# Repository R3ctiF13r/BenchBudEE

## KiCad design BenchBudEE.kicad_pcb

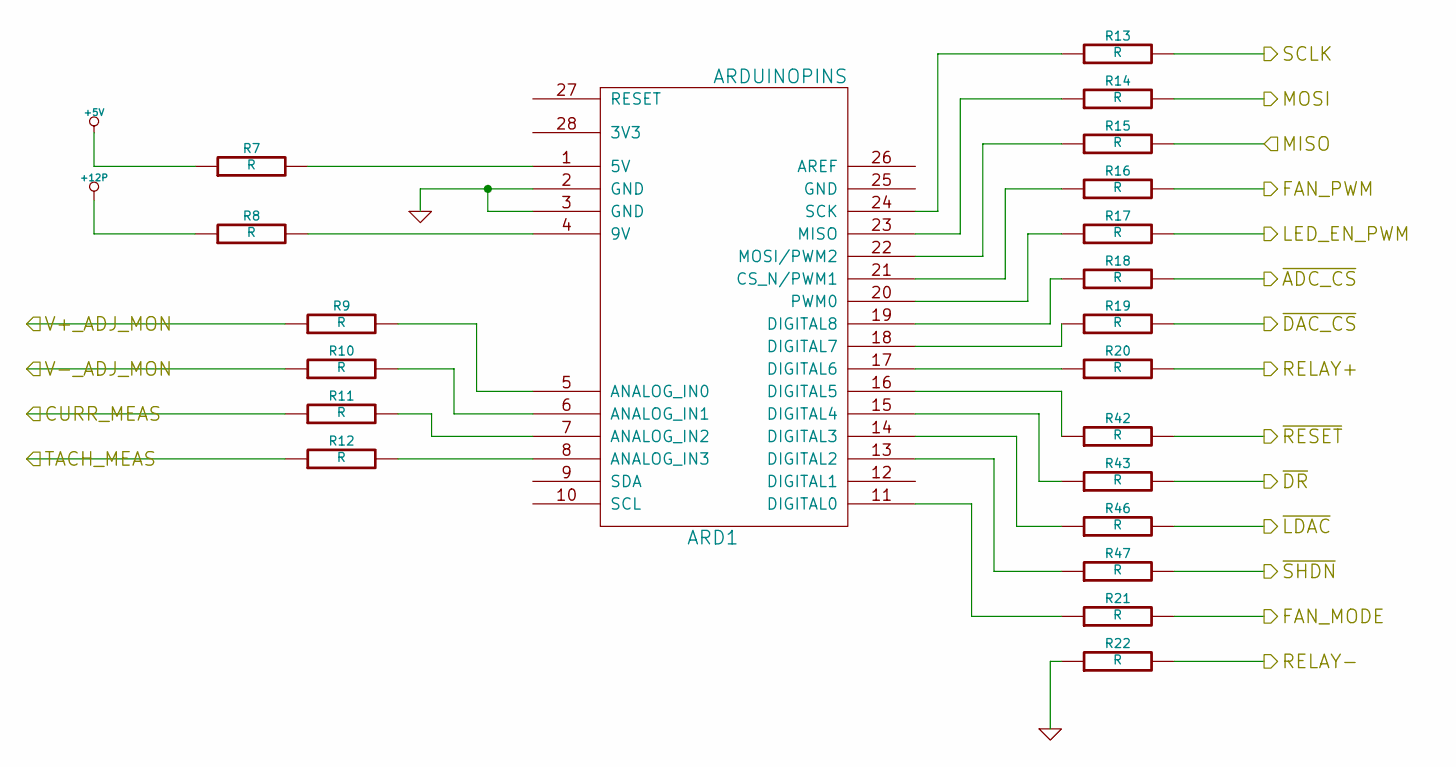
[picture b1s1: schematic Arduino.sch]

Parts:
ARD1: ARDUINOPINS
R7, R8, R9, R10, R11, R12, R13, R14, R15, R16, R17, R18, R19, R20, R21, R22, R42, R43, R46, R47: R

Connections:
+5V: R7.1; also elsewhere on the board
+12P: R8.1; also elsewhere on the board
/Arduino/CURR_MEAS: R11.1; also elsewhere on the board
/Arduino/FAN_MODE: R21.2; also elsewhere on the board
/Arduino/FAN_PWM: R16.2; also elsewhere on the board
/Arduino/LED_EN_PWM: R17.2; also elsewhere on the board
/Arduino/MISO: R15.2; also elsewhere on the board
/Arduino/MOSI: R14.2; also elsewhere on the board
/Arduino/RELAY+: R20.2; also elsewhere on the board
/Arduino/RELAY-: R22.2; also elsewhere on the board
/Arduino/SCLK: R13.2; also elsewhere on the board
/Arduino/V+_ADJ_MON: R9.1; also elsewhere on the board
/Arduino/V-_ADJ_MON: R10.1; also elsewhere on the board
/Arduino/~ADC_CS: R18.2; also elsewhere on the board
/Arduino/~DR: R43.2; also elsewhere on the board
/Arduino/~LDAC: R46.2; also elsewhere on the board
/Arduino/~RESET: R42.2; also elsewhere on the board
/Arduino/~SHDN: R47.2; also elsewhere on the board
/Fan/TACH: R12.1; also elsewhere on the board
/Fan/~CS: R19.2; also elsewhere on the board
GND: ARD1.2 (GND), ARD1.3 (GND), R22.1; also elsewhere on the board
unnamed: ARD1.6 (ANALOG_IN1), R10.2
unnamed: ARD1.5 (ANALOG_IN0), R9.2
unnamed: ARD1.22 (MOSI/PWM2), R15.1
unnamed: ARD1.23 (MISO), R14.1
unnamed: ARD1.24 (SCK), R13.1
unnamed: ARD1.8 (ANALOG_IN3), R12.2
unnamed: ARD1.7 (ANALOG_IN2), R11.2
unnamed: ARD1.14 (DIGITAL3), R46.1
unnamed: ARD1.20 (PWM0), R17.1
unnamed: ARD1.19 (DIGITAL8), R18.1
unnamed: ARD1.16 (DIGITAL5), R42.1
unnamed: ARD1.13 (DIGITAL2), R47.1
unnamed: ARD1.18 (DIGITAL7), R19.1
unnamed: ARD1.17 (DIGITAL6), R20.1
unnamed: ARD1.15 (DIGITAL4), R43.1
unnamed: ARD1.1 (5V), R7.2
unnamed: ARD1.21 (CS_N/PWM1), R16.1
unnamed: ARD1.11 (DIGITAL0), R21.1
unnamed: ARD1.4 (9V), R8.2

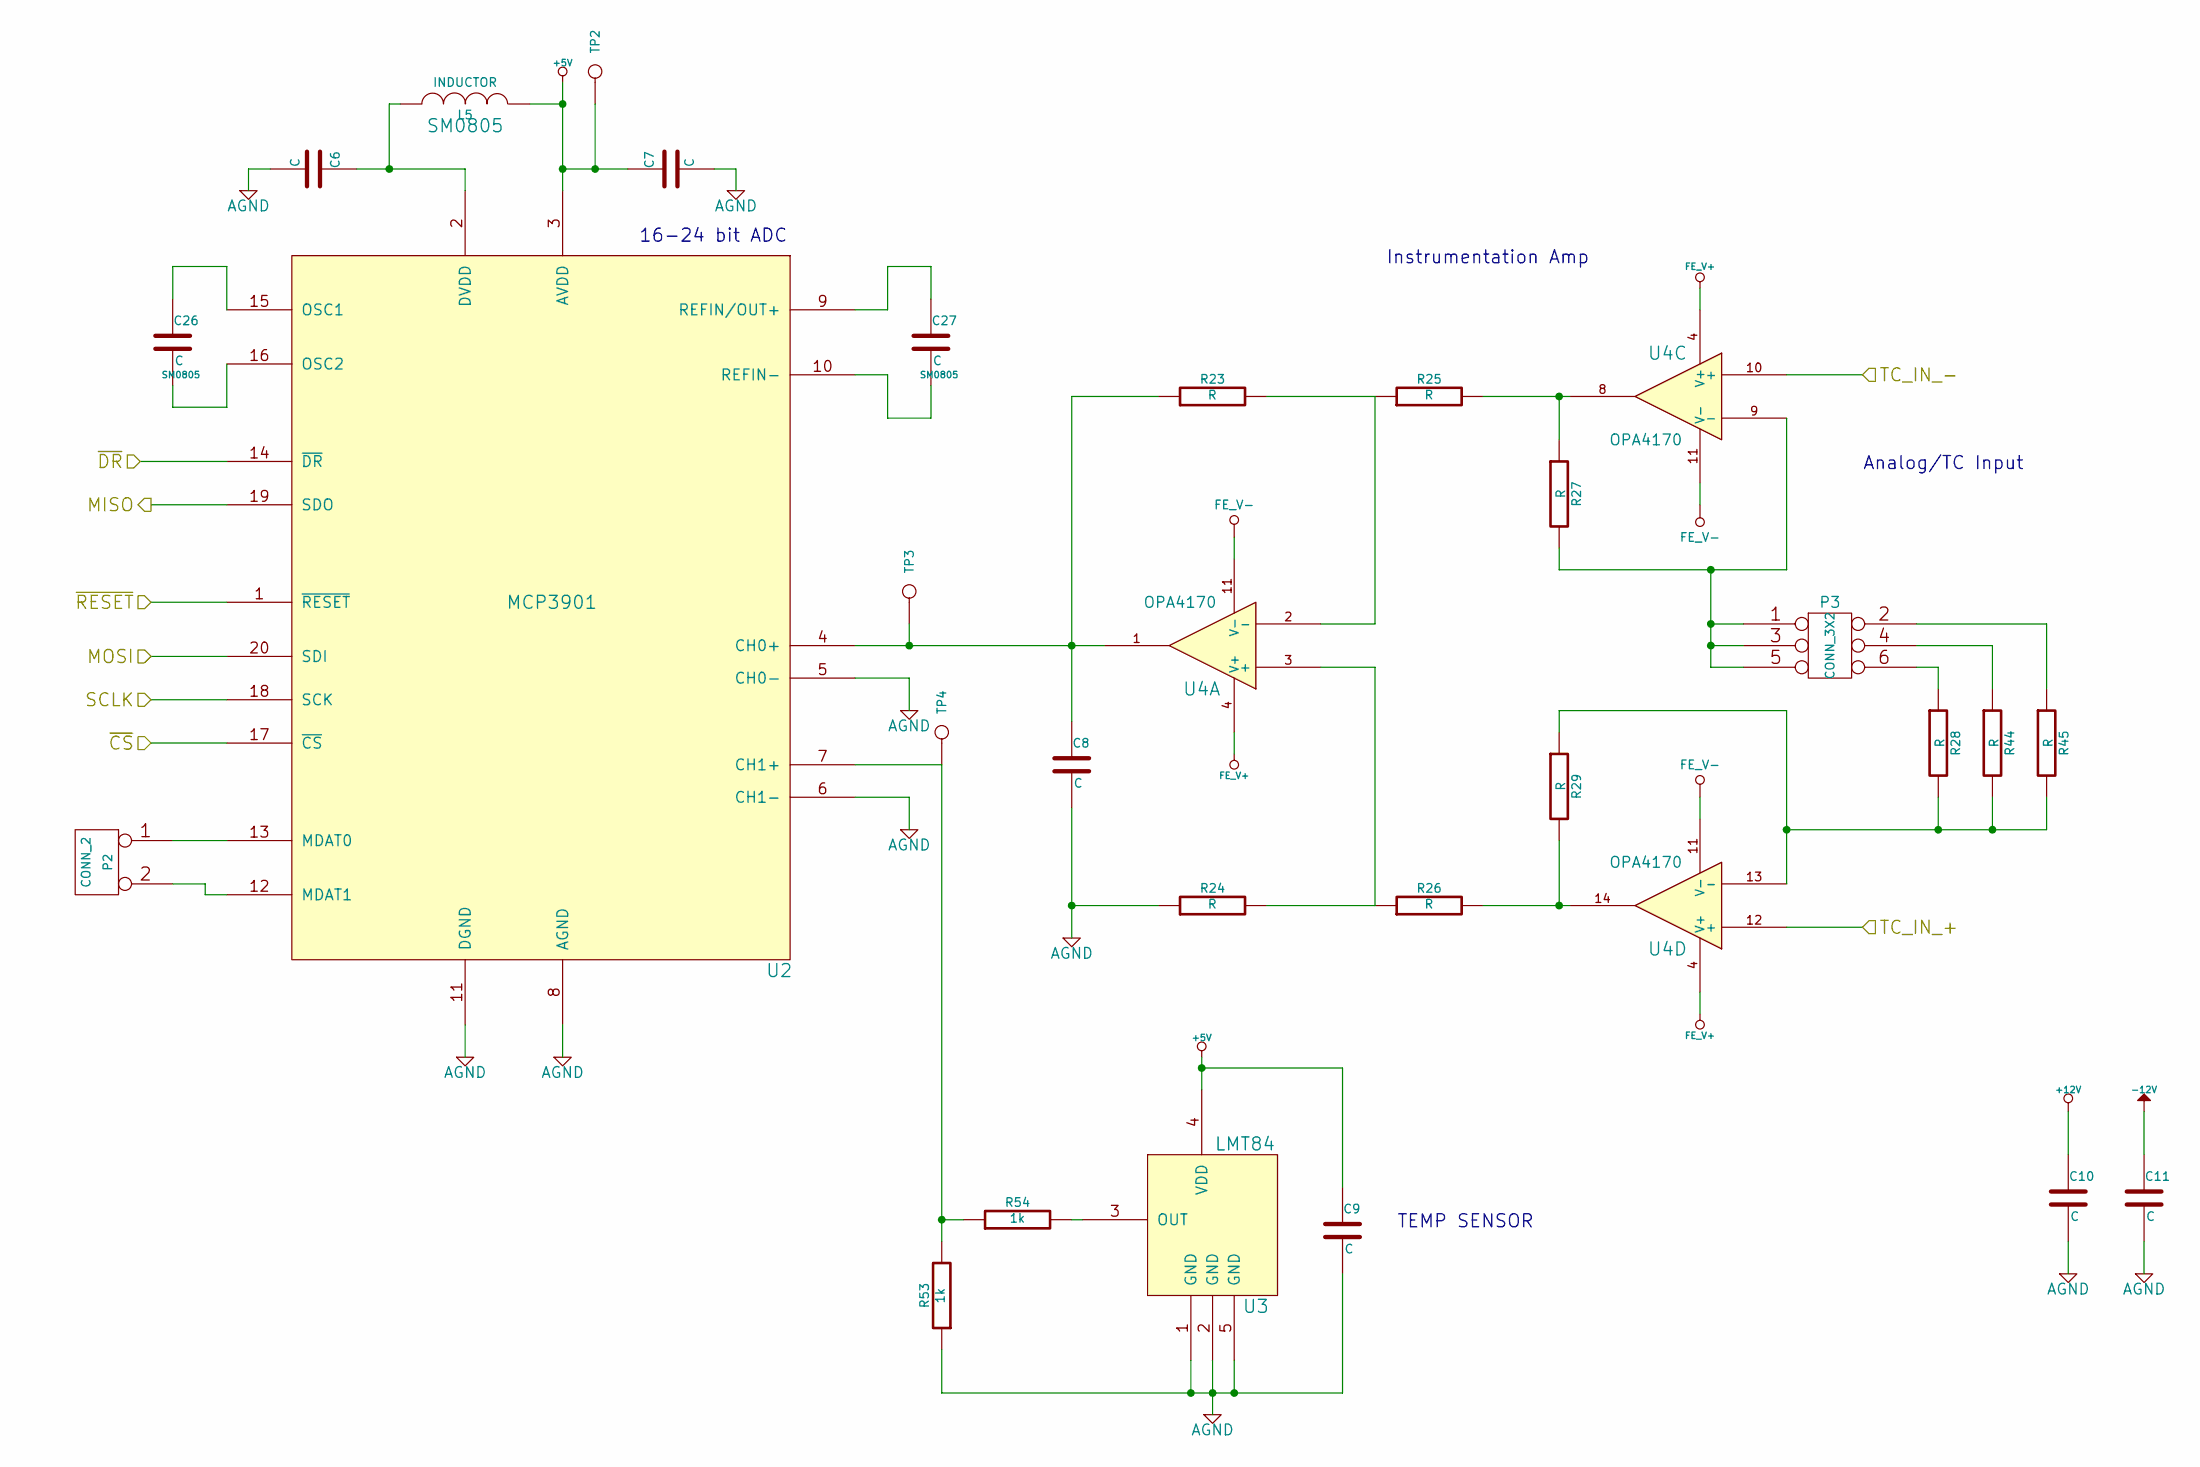
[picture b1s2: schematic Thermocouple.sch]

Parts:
C6, C7, C8, C9, C10, C11: C
C26, C27: C; SM0805
L5: INDUCTOR; SM0805
P2: CONN_2
P3: CONN_3X2
R23, R24, R25, R26, R27, R28, R29, R44, R45: R
R53, R54: 1k
TP2: +5V
TP3: CH0+
TP4: CH1+
U2: MCP3901
U3: LMT84
U4: OPA4170

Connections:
+5V: C7.1, C9.1, L5.1, TP2.1, U2.3 (AVDD), U3.4 (VDD); also elsewhere on the board
+12V: C10.1; also elsewhere on the board
-12V: C11.1; also elsewhere on the board
/Arduino/MISO: U2.19 (SDO); also elsewhere on the board
/Arduino/MOSI: U2.20 (SDI); also elsewhere on the board
/Arduino/SCLK: U2.18 (SCK); also elsewhere on the board
/Arduino/~ADC_CS: U2.17 (~CS); also elsewhere on the board
/Arduino/~DR: U2.14 (~DR); also elsewhere on the board
/Arduino/~RESET: U2.1 (~RESET); also elsewhere on the board
/Terminal_Block/TC_IN_+: U4.12 (+); also elsewhere on the board
/Terminal_Block/TC_IN_-: U4.10 (+); also elsewhere on the board
AGND: C6.2, C7.2, C8.2, C9.2, C10.2, C11.2, R24.1, R53.1, U2.5 (CH0-), U2.6 (CH1-), U2.8 (AGND), U2.11 (DGND), U3.1 (GND), U3.2 (GND), U3.5 (GND); also elsewhere on the board
FE_V+: U4.4 (V+); also elsewhere on the board
FE_V-: U4.11 (V-); also elsewhere on the board
unnamed: C27.1, U2.9 (REFIN/OUT+)
unnamed: C26.1, U2.15 (OSC1)
unnamed: C26.2, U2.16 (OSC2)
unnamed: P2.1, U2.13 (MDAT0)
unnamed: P2.2 (PM), U2.12 (MDAT1)
unnamed: C27.2, U2.10 (REFIN-)
unnamed: R53.2, R54.1, TP4.1, U2.7 (CH1+)
unnamed: R54.2, U3.3 (OUT)
unnamed: C6.1, L5.2, U2.2 (DVDD)
unnamed: C8.1, R23.1, TP3.1, U2.4 (CH0+), U4.1
unnamed: R24.2, R26.1, U4.3 (+)
unnamed: R23.2, R25.1, U4.2 (-)
unnamed: R25.2, R27.1, U4.8
unnamed: R26.2, R29.2, U4.14
unnamed: P3.6, R28.1
unnamed: P3.4, R44.1
unnamed: P3.1, P3.3, P3.5, R27.2, U4.9 (-)
unnamed: P3.2, R45.1
unnamed: R28.2, R29.1, R44.2, R45.2, U4.13 (-)

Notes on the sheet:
Analog/TC Input
Instrumentation Amp
16-24 bit ADC
TEMP SENSOR

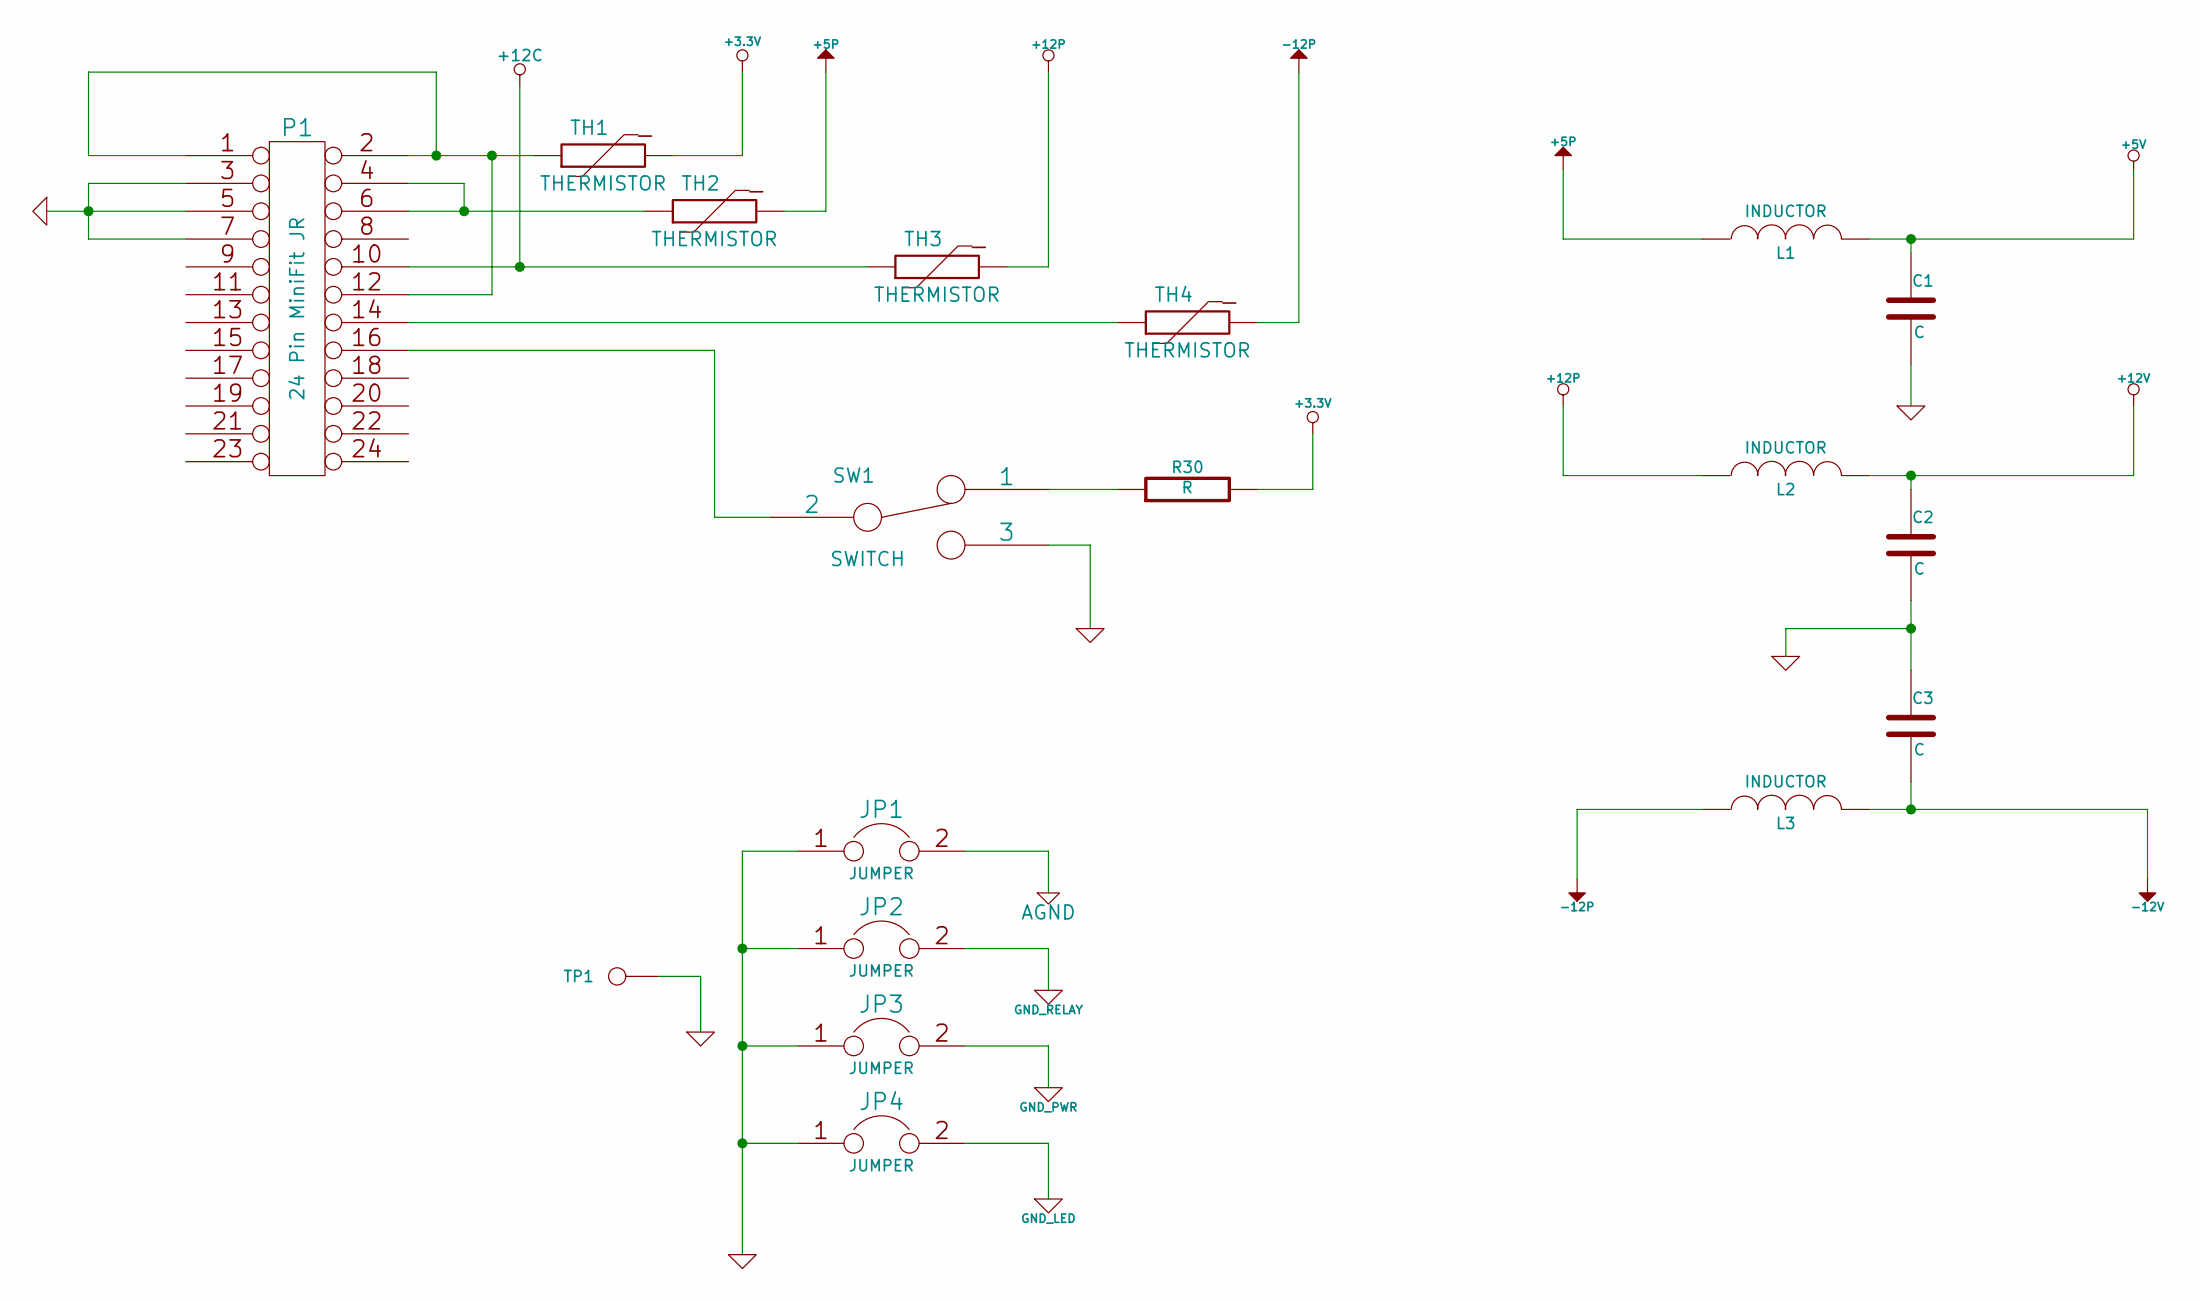
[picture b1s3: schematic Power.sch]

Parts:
C1, C2, C3: C
JP1, JP2, JP3, JP4: JUMPER
L1, L2, L3: INDUCTOR; MFG PART NUM CM322522-220KL
P1: 24 Pin MiniFit JR; MFG PART NUM 39-30-1240
R30: R
SW1: SWITCH; MFG PART NUM OS102011MA1QN1
TH1, TH2, TH3, TH4: THERMISTOR; MFG PART NUM MINISMDC050F-2
TP1: CONN_1

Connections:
+3.3V: R30.2, TH1.2; also elsewhere on the board
+5P: L1.1, TH2.2; also elsewhere on the board
+5V: C1.1, L1.2; also elsewhere on the board
+12C: P1.10, TH3.1; also elsewhere on the board
+12P: L2.1, TH3.2; also elsewhere on the board
+12V: C2.1, L2.2; also elsewhere on the board
-12P: L3.1, TH4.2
-12V: C3.2, L3.2; also elsewhere on the board
AGND: JP1.2; also elsewhere on the board
GND: C1.2, C2.2, C3.1, JP1.1, JP2.1, JP3.1, JP4.1, P1.3, P1.5, P1.7, SW1.3, TP1.1; also elsewhere on the board
GND_LED: JP4.2; also elsewhere on the board
GND_PWR: JP3.2; also elsewhere on the board
GND_RELAY: JP2.2; also elsewhere on the board
unnamed: P1.14, TH4.1
unnamed: P1.4, P1.6, TH2.1
unnamed: R30.1, SW1.1
unnamed: P1.16, SW1.2
unnamed: P1.1, P1.2, P1.12, TH1.1

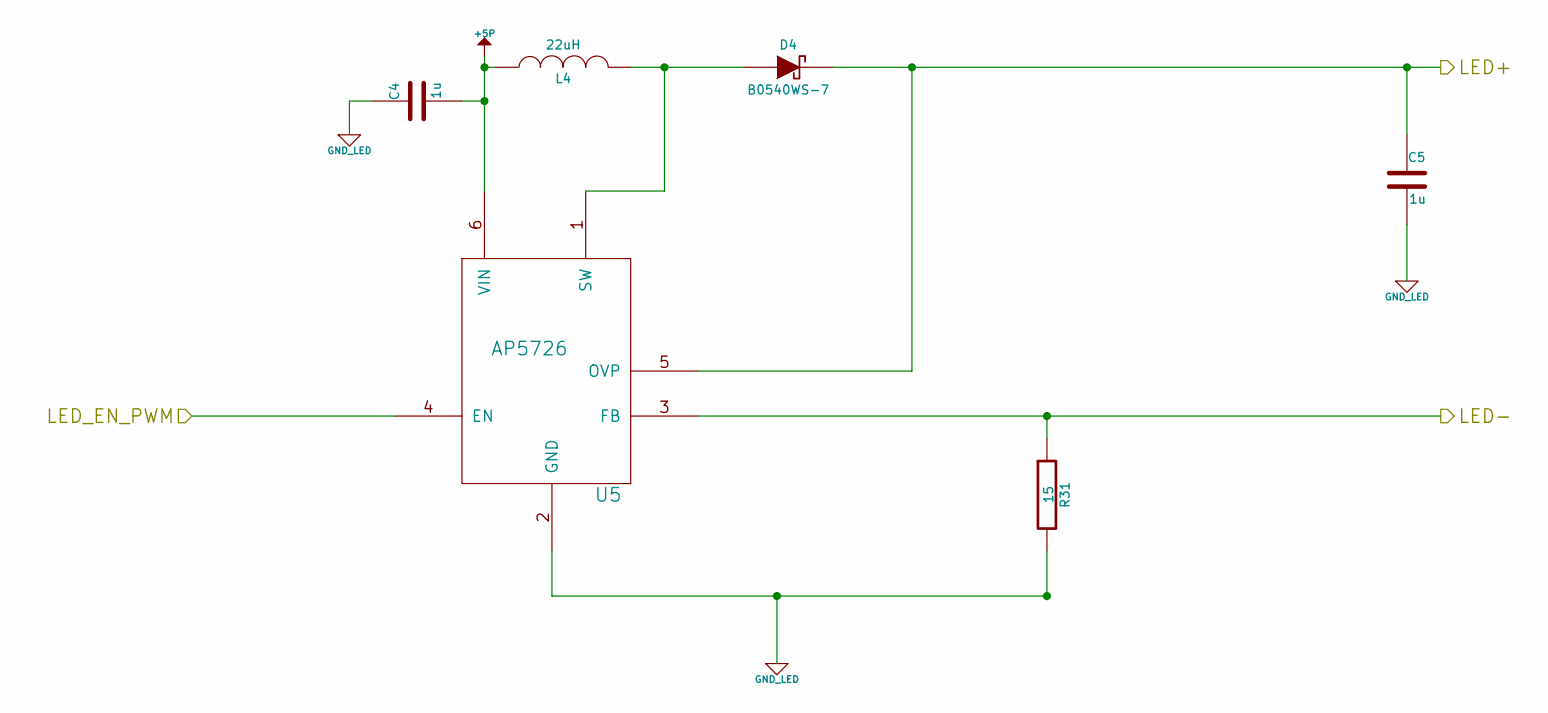
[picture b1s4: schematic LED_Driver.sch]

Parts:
C4, C5: 1u
D4: B0540WS-7; MFG PART NUM B0540WS-7
L4: 22uH; MFG PART NUM NR4012T220M
R31: 15
U5: AP5726; MFG PART NUM AP5726WG-7

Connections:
+5P: C4.2, L4.1, U5.6 (VIN); also elsewhere on the board
/Arduino/LED_EN_PWM: U5.4 (EN); also elsewhere on the board
/LED_Driver/LED+: C5.1, D4.2 (K), U5.5 (OVP); also elsewhere on the board
/LED_Driver/LED-: R31.1, U5.3 (FB); also elsewhere on the board
GND_LED: C4.1, C5.2, R31.2, U5.2 (GND); also elsewhere on the board
unnamed: D4.1 (A), L4.2, U5.1 (SW)

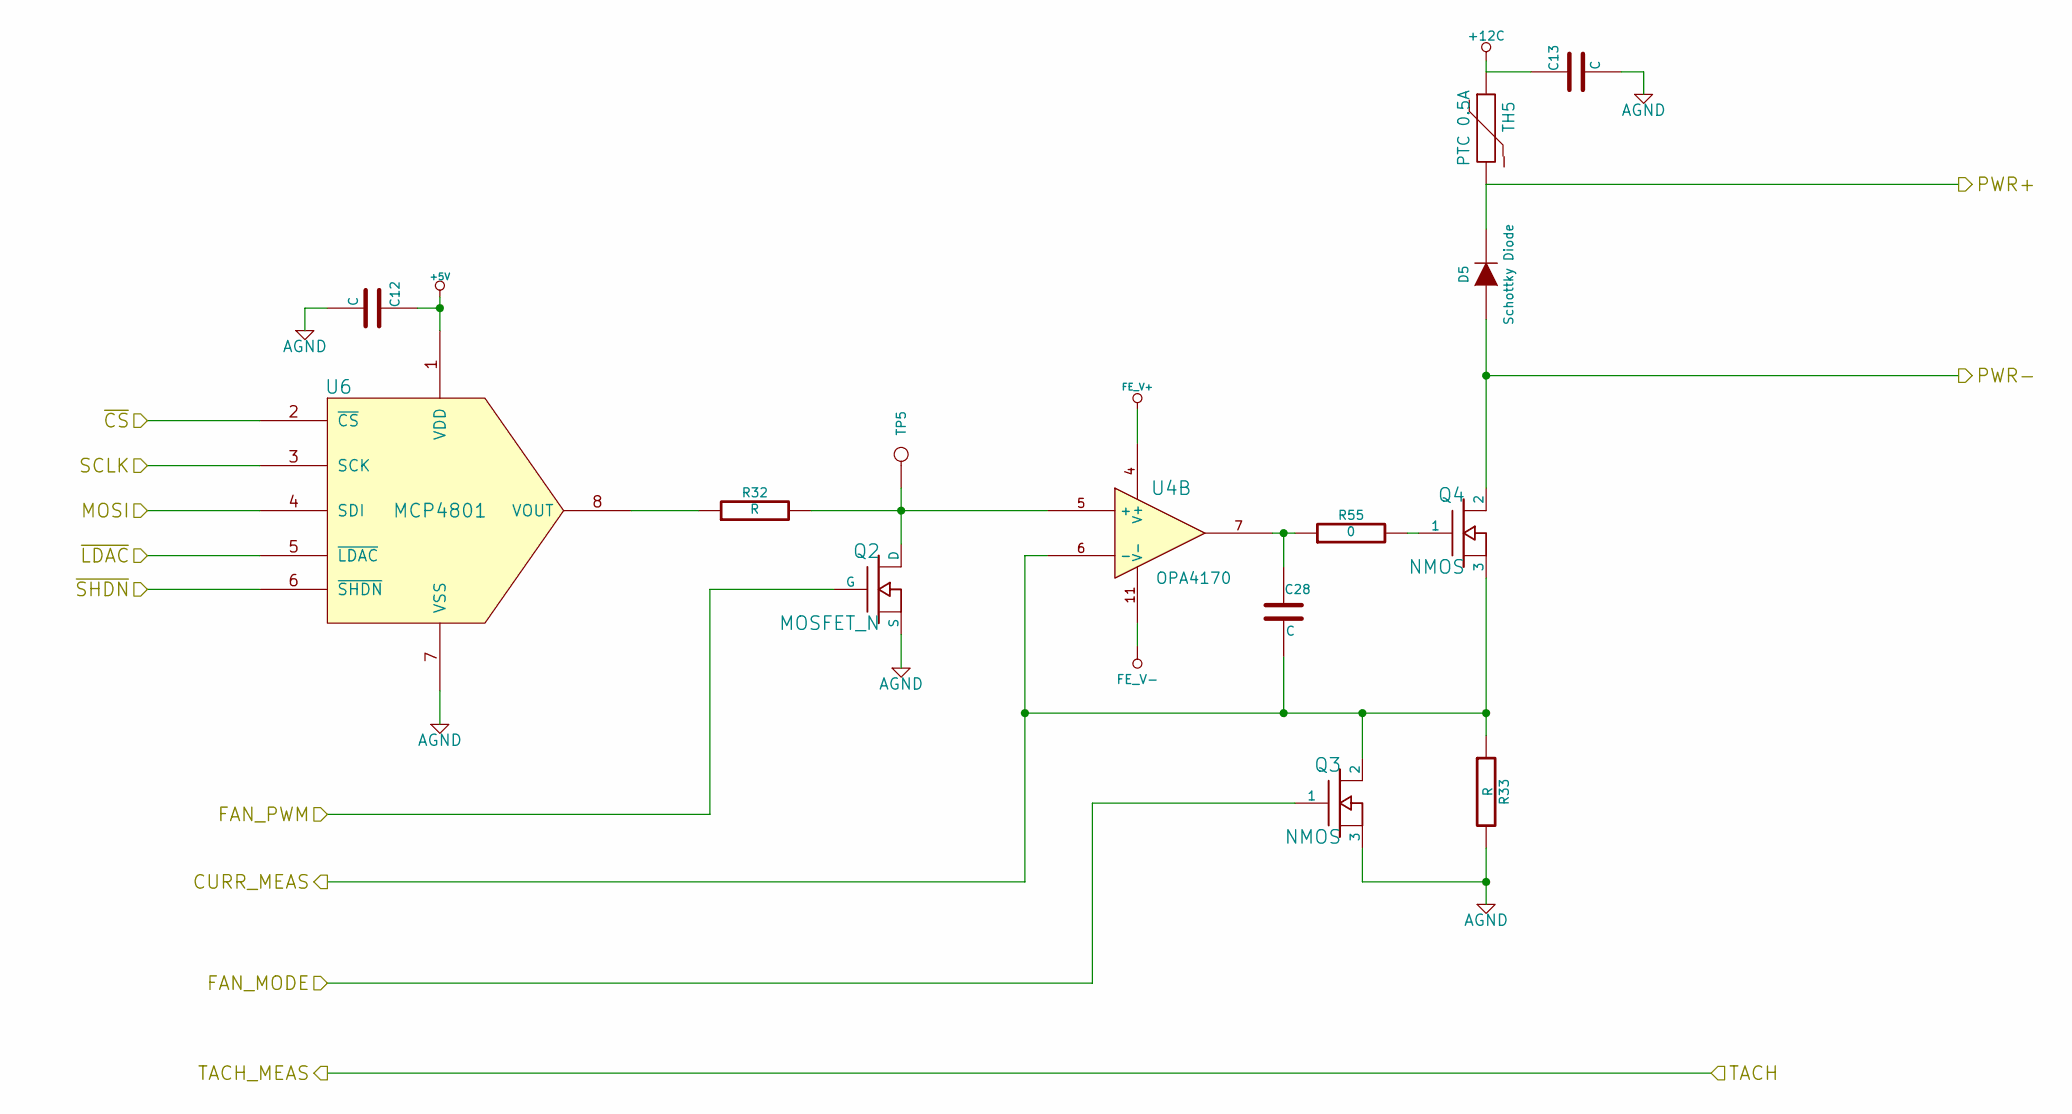
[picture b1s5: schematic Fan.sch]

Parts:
C12, C13, C28: C
D5: Schottky Diode; MFG PART NUM B130-13-F
Q2: MOSFET_N; MFG PART NUM DMN65D8L-7
Q3, Q4: NMOS; MFG PART NUM AOD476
R32, R33: R
R55: 0
TH5: PTC 0.5A; MFG PART NUM MINISMDC050F-2
TP5: DAC_OUT
U4: OPA4170
U6: MCP4801

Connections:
+5V: C12.1, U6.1 (VDD); also elsewhere on the board
+12C: C13.1, TH5.1; also elsewhere on the board
/Arduino/CURR_MEAS: C28.2, Q3.2, Q4.3, R33.1, U4.6 (-); also elsewhere on the board
/Arduino/FAN_MODE: Q3.1; also elsewhere on the board
/Arduino/FAN_PWM: Q2.G; also elsewhere on the board
/Arduino/MOSI: U6.4 (SDI); also elsewhere on the board
/Arduino/SCLK: U6.3 (SCK); also elsewhere on the board
/Arduino/~LDAC: U6.5 (~LDAC); also elsewhere on the board
/Arduino/~SHDN: U6.6 (~SHDN); also elsewhere on the board
/Fan/PWR+: D5.2 (K), TH5.2; also elsewhere on the board
/Fan/PWR-: D5.1 (A), Q4.2; also elsewhere on the board
/Fan/~CS: U6.2 (~CS); also elsewhere on the board
AGND: C12.2, C13.2, Q2.S, Q3.3, R33.2, U6.7 (VSS); also elsewhere on the board
FE_V+: U4.4 (V+); also elsewhere on the board
FE_V-: U4.11 (V-); also elsewhere on the board
unnamed: R32.1, U6.8 (VOUT)
unnamed: Q4.1, R55.2
unnamed: C28.1, R55.1, U4.7
unnamed: Q2.D, R32.2, TP5.1, U4.5 (+)

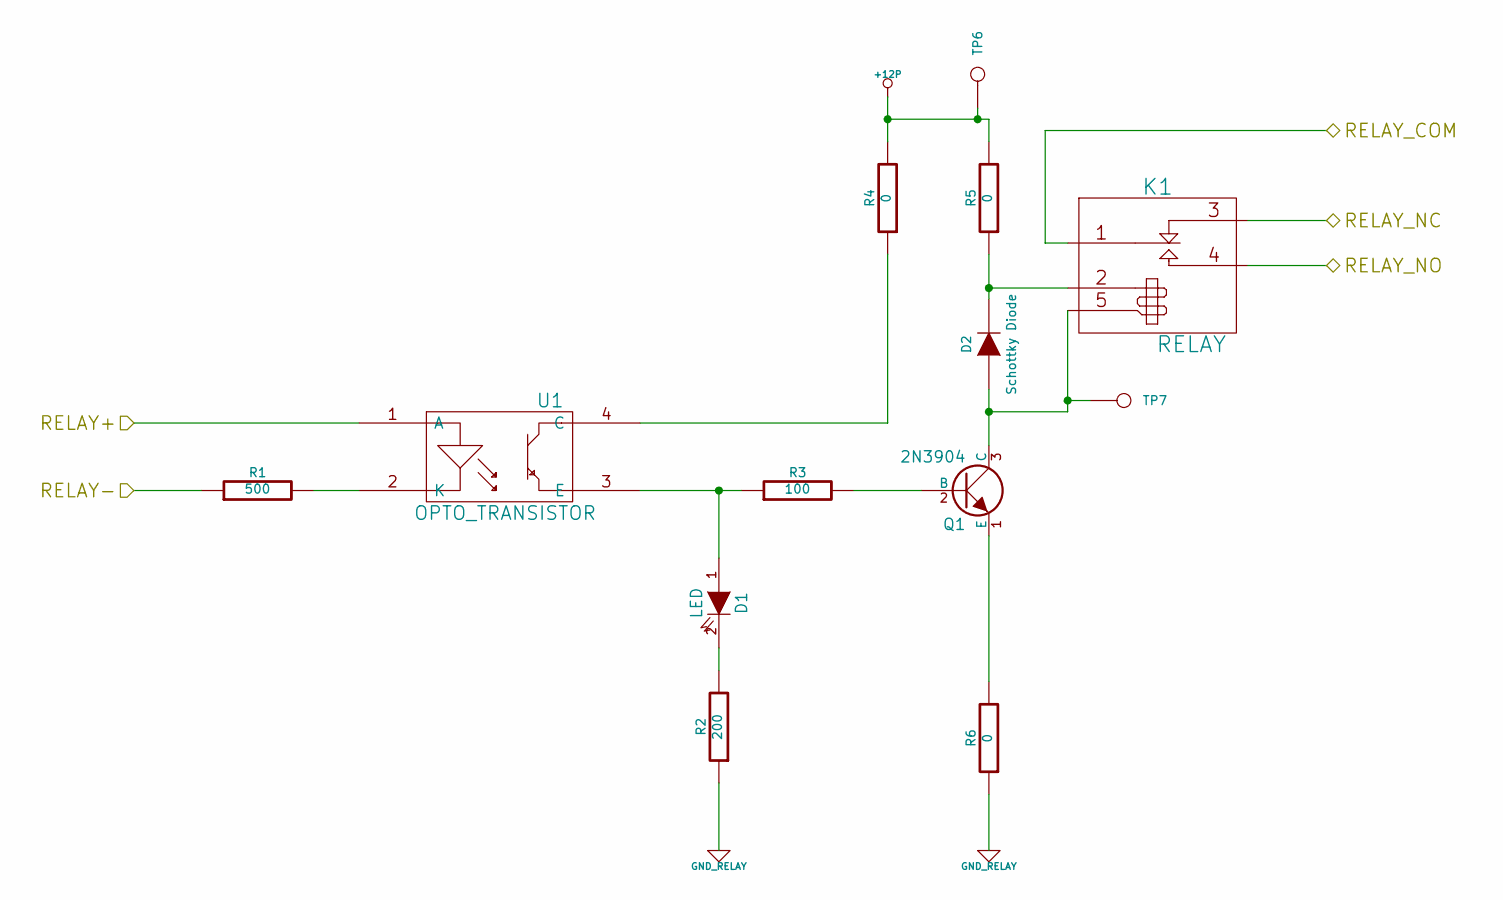
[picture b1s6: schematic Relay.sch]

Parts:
D1: LED; MFG PART NUM LG Q971-KN-1
D2: Schottky Diode; MFG PART NUM B130-13-F
K1: RELAY; MFG PART NUM 1461069-5
Q1: 2N3904; MFG PART NUM MMBT3904-7-F
R1: 500
R2: 200
R3: 100
R4, R5, R6: 0
TP6: +12P
TP7: RLY-
U1: OPTO_TRANSISTOR; MFG PART NUM LTV-816S

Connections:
+12P: R4.2, R5.2, TP6.1; also elsewhere on the board
/Arduino/RELAY+: U1.1 (A); also elsewhere on the board
/Arduino/RELAY-: R1.1; also elsewhere on the board
/Relay/RELAY_COM: K1.1; also elsewhere on the board
/Relay/RELAY_NC: K1.3; also elsewhere on the board
/Relay/RELAY_NO: K1.4; also elsewhere on the board
GND_RELAY: R2.1, R6.1; also elsewhere on the board
unnamed: Q1.1 (E), R6.2
unnamed: Q1.2 (B), R3.2
unnamed: D1.2 (K), R2.2
unnamed: D1.1 (A), R3.1, U1.3 (E)
unnamed: R4.1, U1.4 (C)
unnamed: D2.2 (K), K1.2 (COIL+), R5.1
unnamed: D2.1 (A), K1.5 (COIL-), Q1.3 (C), TP7.1
unnamed: R1.2, U1.2 (K)

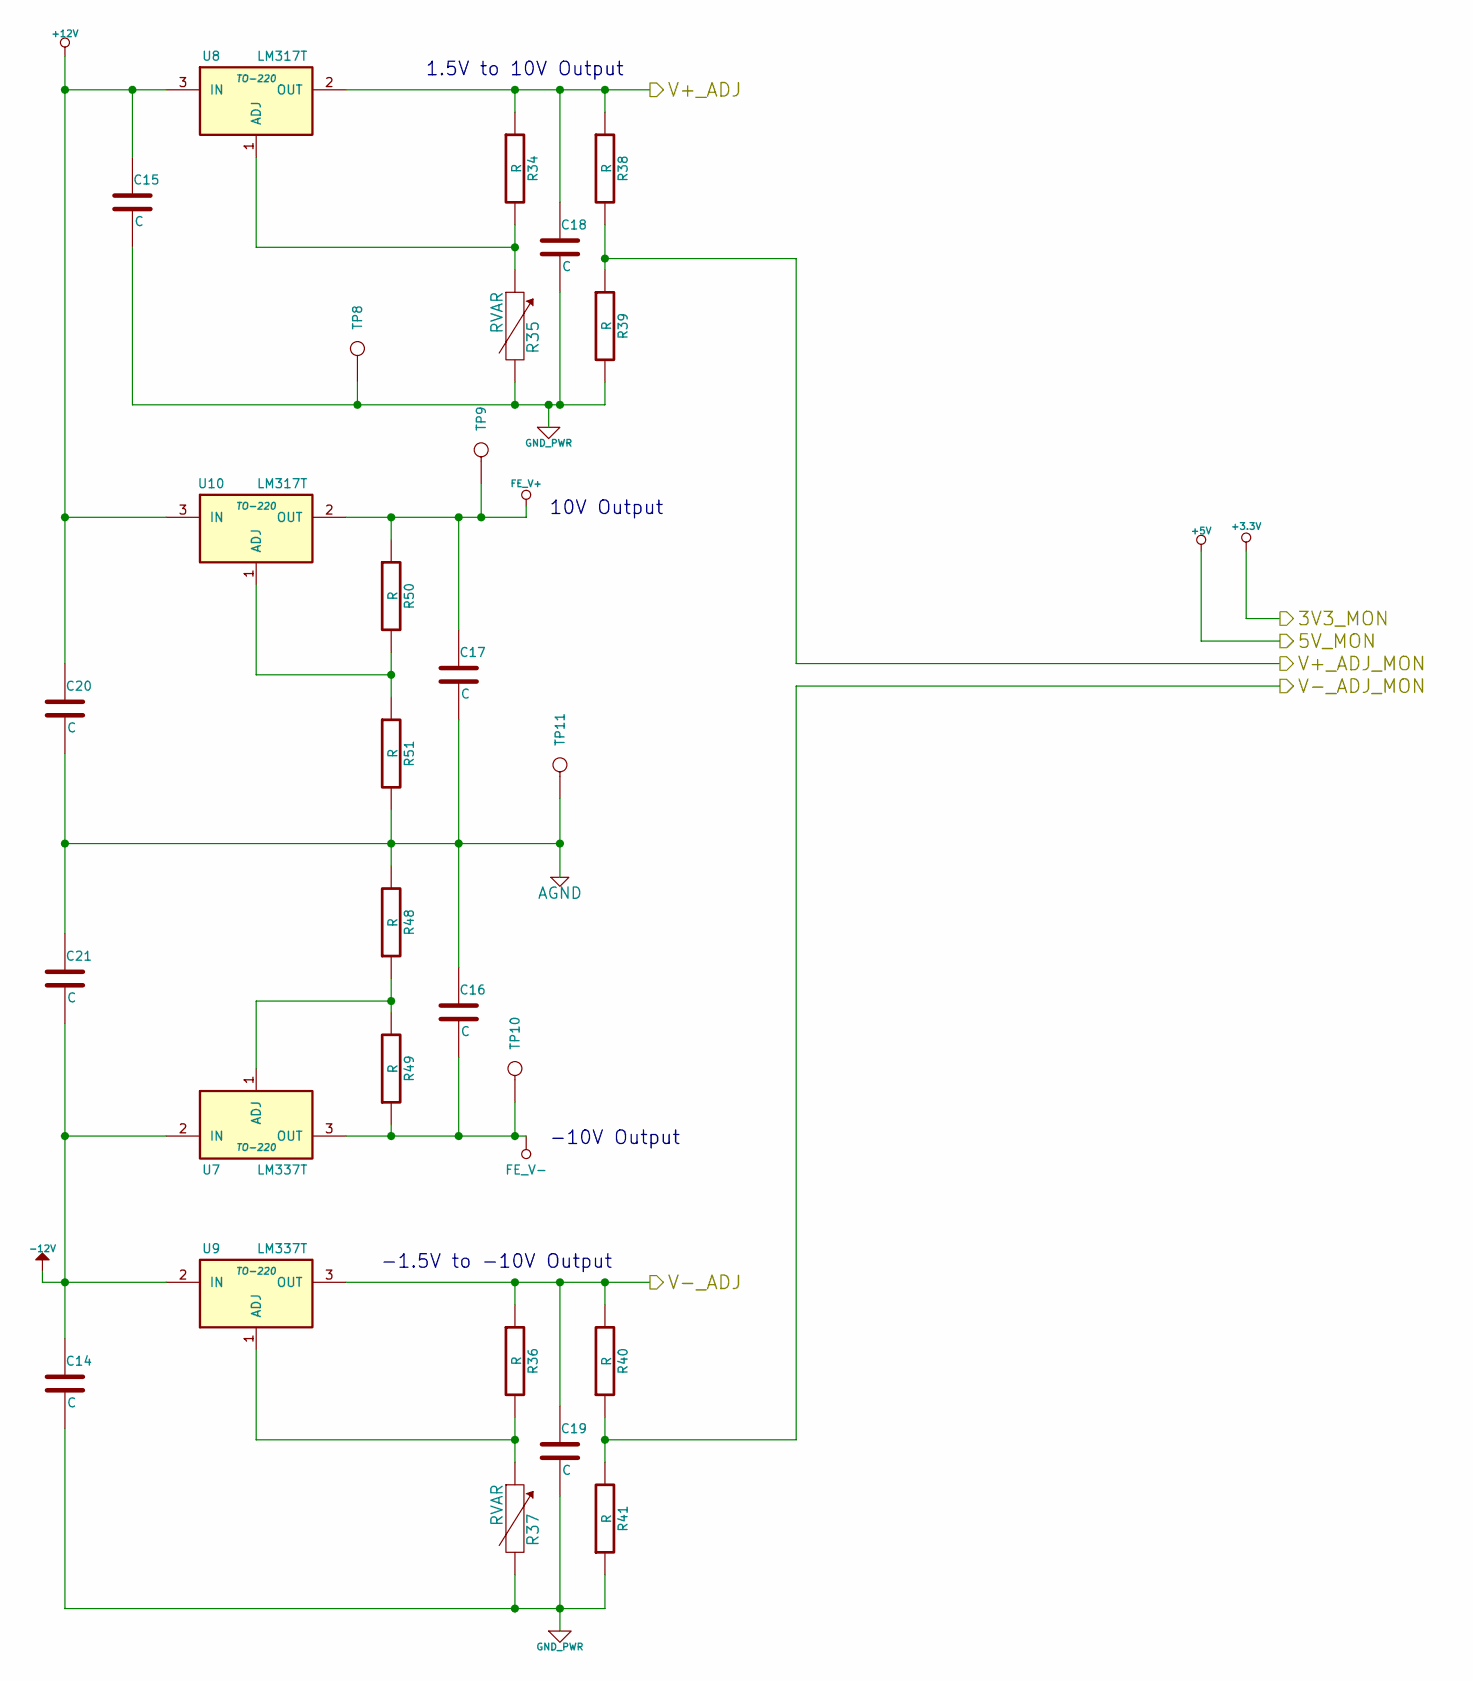
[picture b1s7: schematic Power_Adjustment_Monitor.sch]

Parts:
C14, C15, C16, C17, C18, C19, C20, C21: C
R34, R36, R38, R39, R40, R41, R48, R49, R50, R51: R
R35, R37: RVAR
TP8: GND_PWR
TP9: FE_V+
TP10: FE_V-
TP11: AGND
U7, U9: LM337T; TO-220
U8, U10: LM317T; TO-220

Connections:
+12V: C15.1, C20.1, U8.3 (IN), U10.3 (IN); also elsewhere on the board
-12V: C14.1, C21.2, U7.2 (IN), U9.2 (IN); also elsewhere on the board
/Arduino/V+_ADJ_MON: R38.2, R39.1; also elsewhere on the board
/Arduino/V-_ADJ_MON: R40.1, R41.2; also elsewhere on the board
/Power_Adjustment_Monitor/V+_ADJ: C18.1, R34.1, R38.1, U8.2 (OUT); also elsewhere on the board
/Power_Adjustment_Monitor/V-_ADJ: C19.1, R36.1, R40.2, U9.3 (OUT); also elsewhere on the board
AGND: C16.1, C17.2, C20.2, C21.1, R48.2, R51.2, TP11.1; also elsewhere on the board
FE_V+: C17.1, R50.1, TP9.1, U10.2 (OUT); also elsewhere on the board
FE_V-: C16.2, R49.1, TP10.1, U7.3 (OUT); also elsewhere on the board
GND_PWR: C14.2, C15.2, C18.2, C19.2, R35.2, R37.2, R39.2, R41.1, TP8.1; also elsewhere on the board
unnamed: R50.2, R51.1, U10.1 (ADJ)
unnamed: R48.1, R49.2, U7.1 (ADJ)
unnamed: R36.2, R37.1, U9.1 (ADJ)
unnamed: R34.2, R35.1, U8.1 (ADJ)

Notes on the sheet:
1.5V to 10V Output
10V Output
-1.5V to -10V Output
-10V Output

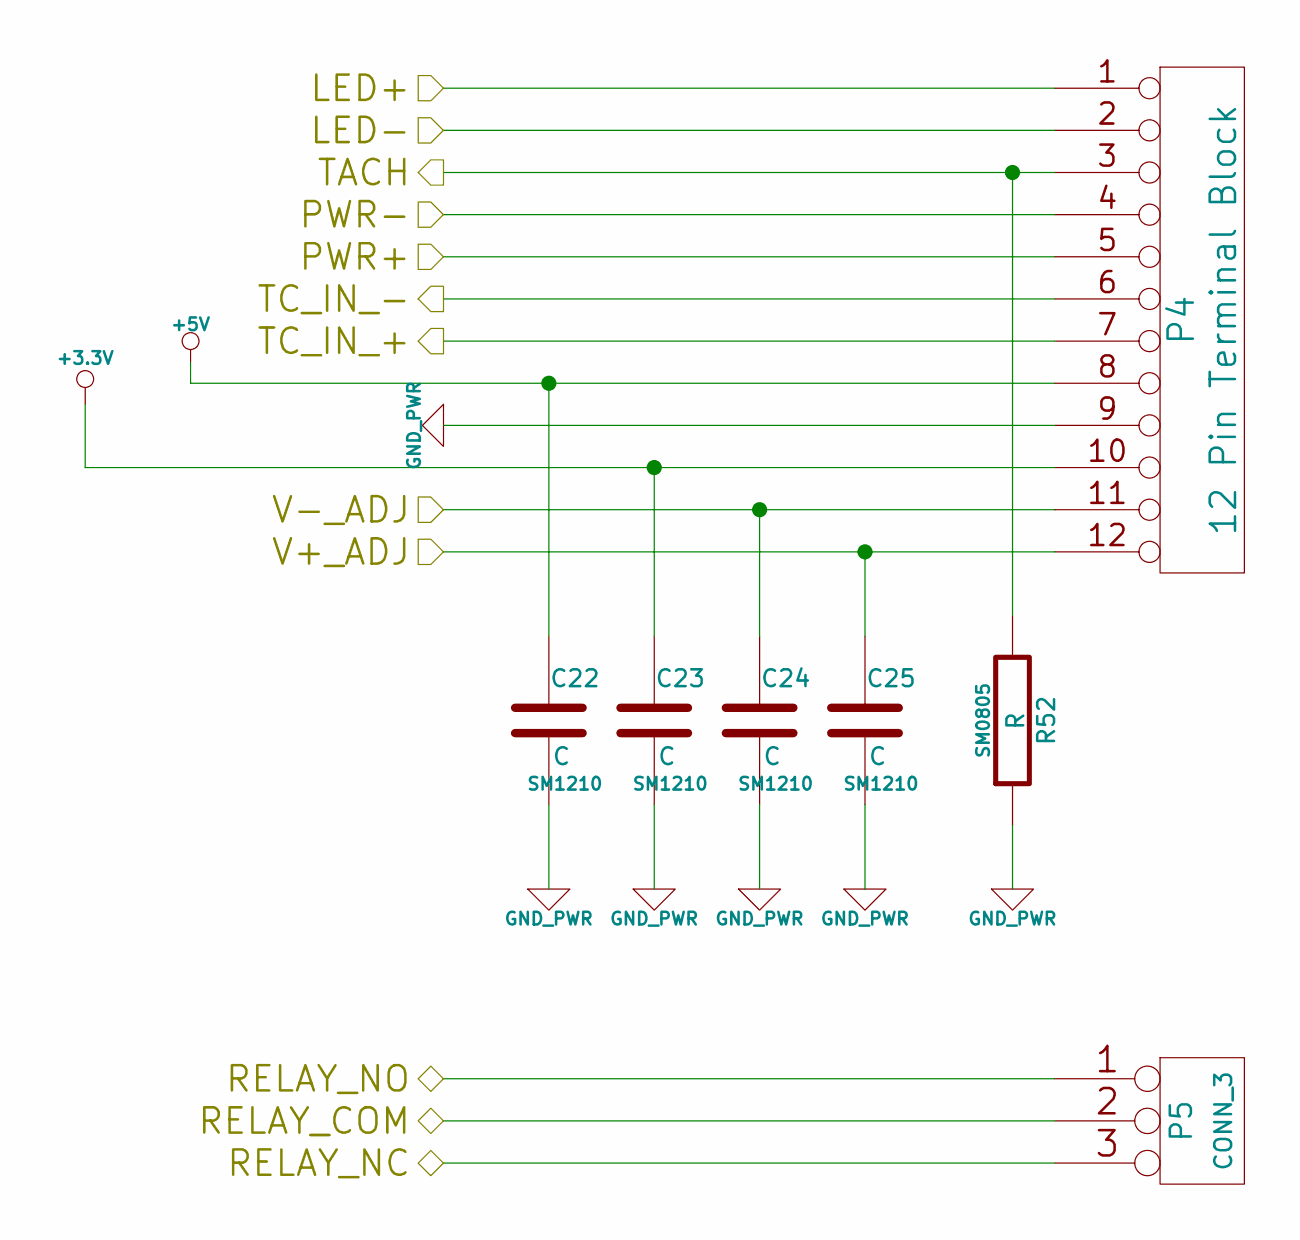
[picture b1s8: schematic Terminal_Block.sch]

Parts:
C22, C23, C24, C25: C; SM1210
P4: 12 Pin Terminal Block; MFG PART NUM OSTTE120104
P5: CONN_3; MFG PART NUM 1935174
R52: R; SM0805

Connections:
+3.3V: C23.1, P4.10; also elsewhere on the board
+5V: C22.1, P4.8; also elsewhere on the board
/Fan/PWR+: P4.5; also elsewhere on the board
/Fan/PWR-: P4.4; also elsewhere on the board
/Fan/TACH: P4.3, R52.2; also elsewhere on the board
/LED_Driver/LED+: P4.1; also elsewhere on the board
/LED_Driver/LED-: P4.2; also elsewhere on the board
/Power_Adjustment_Monitor/V+_ADJ: C25.1, P4.12; also elsewhere on the board
/Power_Adjustment_Monitor/V-_ADJ: C24.1, P4.11; also elsewhere on the board
/Relay/RELAY_COM: P5.2 (PM); also elsewhere on the board
/Relay/RELAY_NC: P5.3; also elsewhere on the board
/Relay/RELAY_NO: P5.1; also elsewhere on the board
/Terminal_Block/TC_IN_+: P4.7; also elsewhere on the board
/Terminal_Block/TC_IN_-: P4.6; also elsewhere on the board
GND_PWR: C22.2, C23.2, C24.2, C25.2, P4.9, R52.1; also elsewhere on the board
